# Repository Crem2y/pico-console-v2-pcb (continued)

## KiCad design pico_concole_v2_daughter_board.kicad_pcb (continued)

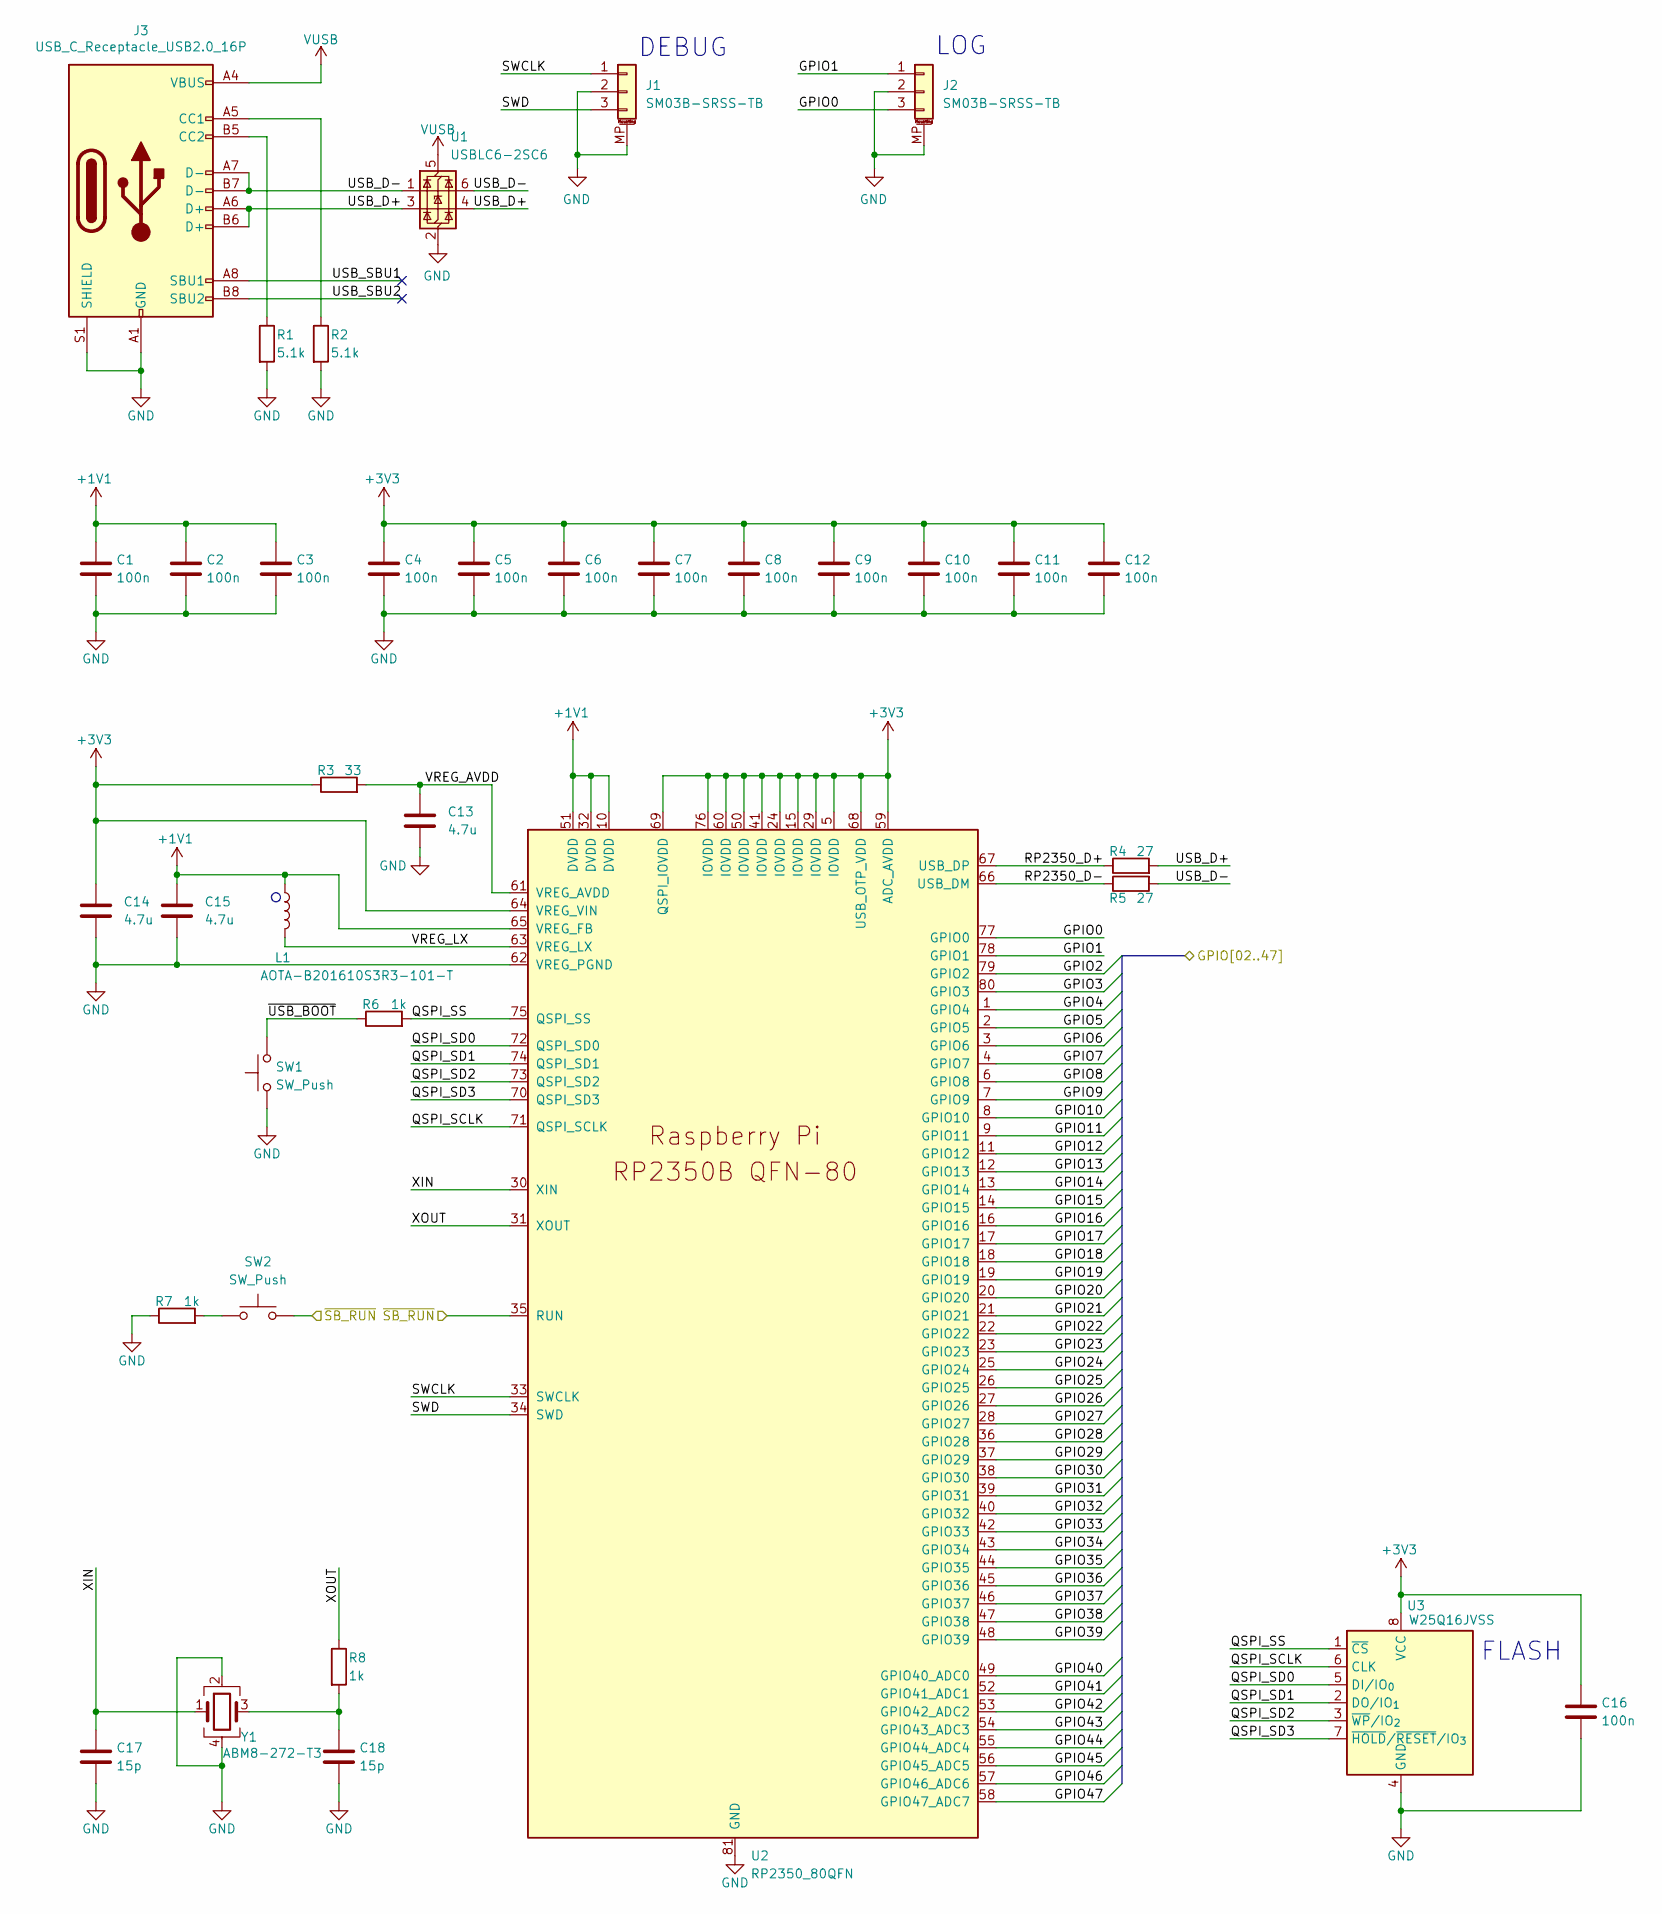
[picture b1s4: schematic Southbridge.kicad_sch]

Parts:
C1, C2, C3, C4, C5, C6, C7, C8, C9, C10, C11, C12, C16: 100n; C_0402_1005Metric_Pad0.74x0.62mm_HandSolder
C13, C14, C15: 4.7u; C_0603_1608Metric_Pad1.08x0.95mm_HandSolder
C17, C18: 15p; C_0402_1005Metric_Pad0.74x0.62mm_HandSolder
J1, J2: SM03B-SRSS-TB; JST_SH_SM03B-SRSS-TB_1x03-1MP_P1.00mm_Horizontal
J3: USB_C_Receptacle_USB2.0_16P; USB_C_Receptacle_HRO_TYPE-C-31-M-12
L1: AOTA-B201610S3R3-101-T; L_pol_2016
R1, R2: 5.1k; R_0805_2012Metric_Pad1.20x1.40mm_HandSolder
R3: 33; C_0402_1005Metric_Pad0.74x0.62mm_HandSolder
R4, R5: 27; R_0402_1005Metric_Pad0.72x0.64mm_HandSolder
R6, R7, R8: 1k; R_0402_1005Metric_Pad0.72x0.64mm_HandSolder
SW1, SW2: SW_Push; SW_Push_1P1T_NO_Vertical_Wuerth_434133025816
U1: USBLC6-2SC6; SOT-23-6
U2: RP2350_80QFN; QFN-80-1EP_10x10mm_P0.4mm_EP3.4x3.4mm; LCSC PN C42415655
U3: W25Q16JVSS; SOIC-8_5.3x5.3mm_P1.27mm
Y1: ABM8-272-T3; Crystal_SMD_3225-4Pin_3.2x2.5mm; LCSC PN C20625731

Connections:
+1V1: C1.1, C2.1, C3.1, C15.1, L1.1, U2.10 (DVDD), U2.32 (DVDD), U2.51 (DVDD), U2.65 (VREG_FB)
+3V3: C4.1, C5.1, C6.1, C7.1, C8.1, C9.1, C10.1, C11.1, C12.1, C14.1, C16.1, R3.1, U2.5 (IOVDD), U2.15 (IOVDD), U2.24 (IOVDD), U2.29 (IOVDD), U2.41 (IOVDD), U2.50 (IOVDD), U2.59 (ADC_AVDD), U2.60 (IOVDD), U2.64 (VREG_VIN), U2.68 (USB_OTP_VDD), U2.69 (QSPI_IOVDD), U2.76 (IOVDD), U3.8 (VCC); also elsewhere on the board
/Daughterboard/GPIO2: U2.79 (GPIO2); also elsewhere on the board
/Daughterboard/GPIO3: U2.80 (GPIO3); also elsewhere on the board
/Daughterboard/GPIO6: U2.3 (GPIO6); also elsewhere on the board
/Daughterboard/GPIO7: U2.4 (GPIO7); also elsewhere on the board
/Daughterboard/GPIO8: U2.6 (GPIO8); also elsewhere on the board
/Daughterboard/GPIO9: U2.7 (GPIO9); also elsewhere on the board
/Daughterboard/GPIO10: U2.8 (GPIO10); also elsewhere on the board
/Daughterboard/GPIO11: U2.9 (GPIO11); also elsewhere on the board
/Daughterboard/GPIO12: U2.11 (GPIO12); also elsewhere on the board
/Daughterboard/GPIO13: U2.12 (GPIO13); also elsewhere on the board
/Daughterboard/GPIO14: U2.13 (GPIO14); also elsewhere on the board
/Daughterboard/GPIO15: U2.14 (GPIO15); also elsewhere on the board
/Daughterboard/GPIO16: U2.16 (GPIO16); also elsewhere on the board
/Daughterboard/GPIO17: U2.17 (GPIO17); also elsewhere on the board
/Daughterboard/GPIO18: U2.18 (GPIO18); also elsewhere on the board
/Daughterboard/GPIO19: U2.19 (GPIO19); also elsewhere on the board
/Daughterboard/GPIO20: U2.20 (GPIO20); also elsewhere on the board
/Daughterboard/GPIO21: U2.21 (GPIO21); also elsewhere on the board
/Daughterboard/GPIO22: U2.22 (GPIO22); also elsewhere on the board
/Daughterboard/GPIO23: U2.23 (GPIO23); also elsewhere on the board
/Daughterboard/GPIO24: U2.25 (GPIO24); also elsewhere on the board
/Daughterboard/GPIO25: U2.26 (GPIO25); also elsewhere on the board
/Daughterboard/GPIO26: U2.27 (GPIO26); also elsewhere on the board
/Daughterboard/GPIO27: U2.28 (GPIO27); also elsewhere on the board
/Daughterboard/GPIO28: U2.36 (GPIO28); also elsewhere on the board
/Daughterboard/GPIO29: U2.37 (GPIO29); also elsewhere on the board
/Daughterboard/GPIO30: U2.38 (GPIO30); also elsewhere on the board
/Daughterboard/GPIO31: U2.39 (GPIO31); also elsewhere on the board
/Daughterboard/GPIO32: U2.40 (GPIO32); also elsewhere on the board
/Daughterboard/GPIO33: U2.42 (GPIO33); also elsewhere on the board
/Daughterboard/GPIO34: U2.43 (GPIO34); also elsewhere on the board
/Daughterboard/GPIO35: U2.44 (GPIO35); also elsewhere on the board
/Daughterboard/GPIO36: U2.45 (GPIO36); also elsewhere on the board
/Daughterboard/GPIO37: U2.46 (GPIO37); also elsewhere on the board
/Daughterboard/GPIO38: U2.47 (GPIO38); also elsewhere on the board
/Daughterboard/GPIO39: U2.48 (GPIO39); also elsewhere on the board
/Daughterboard/GPIO40: U2.49 (GPIO40_ADC0); also elsewhere on the board
/Daughterboard/GPIO41: U2.52 (GPIO41_ADC1); also elsewhere on the board
/Daughterboard/GPIO42: U2.53 (GPIO42_ADC2); also elsewhere on the board
/Daughterboard/GPIO43: U2.54 (GPIO43_ADC3); also elsewhere on the board
/Daughterboard/GPIO44: U2.55 (GPIO44_ADC4); also elsewhere on the board
/Daughterboard/GPIO45: U2.56 (GPIO45_ADC5); also elsewhere on the board
/Daughterboard/GPIO46: U2.57 (GPIO46_ADC6); also elsewhere on the board
/Daughterboard/GPIO47: U2.58 (GPIO47_ADC7); also elsewhere on the board
/Daughterboard/MAIN_GPIO12: U2.2 (GPIO5); also elsewhere on the board
/Daughterboard/MAIN_GPIO13: U2.1 (GPIO4); also elsewhere on the board
/Daughterboard/~SB_RUN: SW2.2, U2.35 (RUN); also elsewhere on the board
/Southbridge/GPIO0: J2.3, U2.77 (GPIO0)
/Southbridge/GPIO1: J2.1, U2.78 (GPIO1)
/Southbridge/QSPI_SCLK: U2.71 (QSPI_SCLK), U3.6 (CLK)
/Southbridge/QSPI_SD0: U2.72 (QSPI_SD0), U3.5 (DI/IO_{0})
/Southbridge/QSPI_SD1: U2.74 (QSPI_SD1), U3.2 (DO/IO_{1})
/Southbridge/QSPI_SD2: U2.73 (QSPI_SD2), U3.3 (~WP/IO_{2})
/Southbridge/QSPI_SD3: U2.70 (QSPI_SD3), U3.7 (~HOLD/~RESET/IO_{3})
/Southbridge/QSPI_SS: R6.2, U2.75 (QSPI_SS), U3.1 (~CS)
/Southbridge/RP2350_D+: R4.1, U2.67 (USB_DP)
/Southbridge/RP2350_D-: R5.1, U2.66 (USB_DM)
/Southbridge/SWCLK: J1.1, U2.33 (SWCLK)
/Southbridge/SWD: J1.3, U2.34 (SWD)
/Southbridge/USB_D+: J3.A6 (D+), J3.B6 (D+), R4.2, U1.3 (I/O2), U1.4 (I/O2)
/Southbridge/USB_D-: J3.A7 (D-), J3.B7 (D-), R5.2, U1.1 (I/O1), U1.6 (I/O1)
/Southbridge/USB_SBU1: J3.A8 (SBU1)
/Southbridge/USB_SBU2: J3.B8 (SBU2)
/Southbridge/VREG_AVDD: C13.1, R3.2, U2.61 (VREG_AVDD)
/Southbridge/VREG_LX: L1.2, U2.63 (VREG_LX)
/Southbridge/XIN: C17.1, U2.30 (XIN), Y1.1
/Southbridge/XOUT: R8.1, U2.31 (XOUT)
/Southbridge/~USB_BOOT: R6.1, SW1.2
GND: C1.2, C2.2, C3.2, C4.2, C5.2, C6.2, C7.2, C8.2, C9.2, C10.2, C11.2, C12.2, C13.2, C14.2, C15.2, C16.2, C17.2, C18.2, J1.2, J1.MP (MountPin), J2.2, J2.MP (MountPin), J3.A1 (GND), J3.A12 (GND), J3.B1 (GND), J3.B12 (GND), J3.S1 (SHIELD), R1.2, R2.2, R7.1, SW1.1, U1.2 (GND), U2.62 (VREG_PGND), U2.81 (GND), U3.4 (GND), Y1.2, Y1.4; also elsewhere on the board
unnamed: C18.1, R8.2, Y1.3
unnamed: J3.A5 (CC1), R2.1
unnamed: J3.B5 (CC2), R1.1
unnamed: R7.2, SW2.1
VUSB: J3.A4 (VBUS), J3.A9 (VBUS), J3.B4 (VBUS), J3.B9 (VBUS), U1.5 (VBUS); also elsewhere on the board

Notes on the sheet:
LOG
DEBUG
FLASH

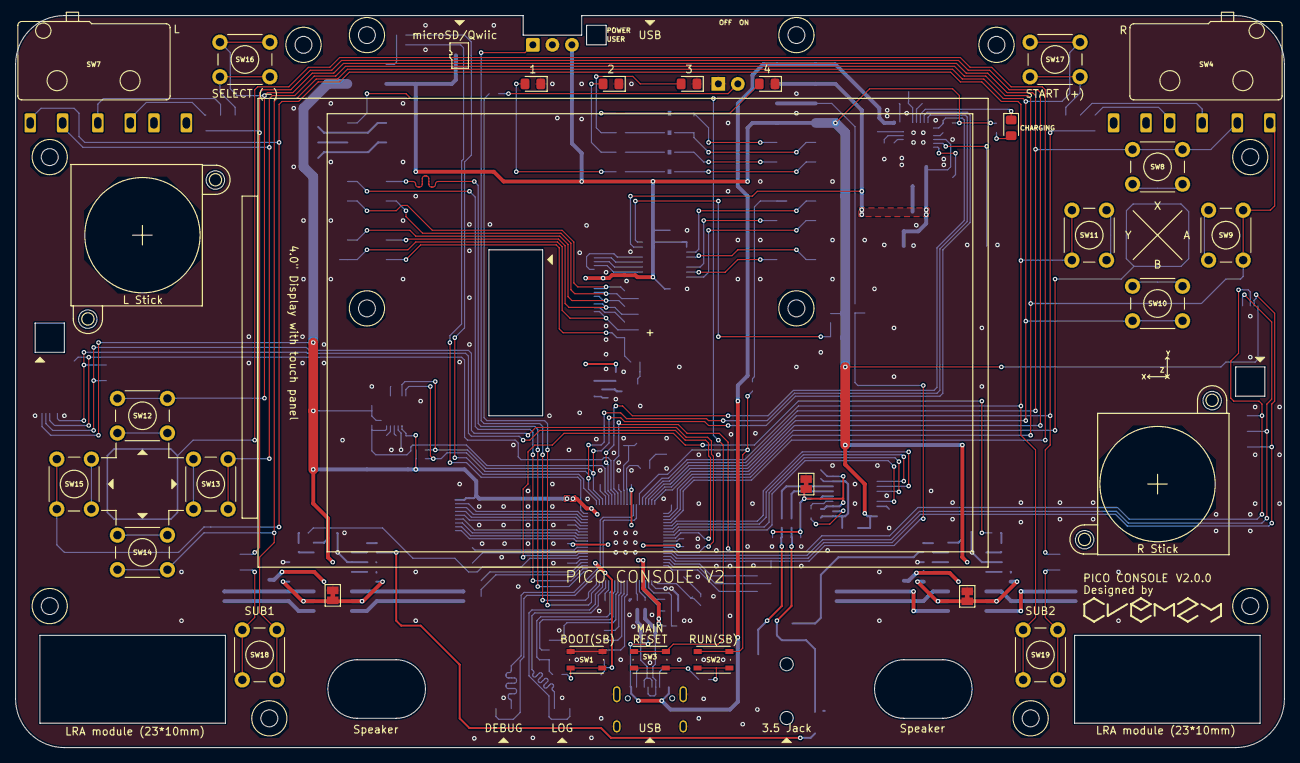
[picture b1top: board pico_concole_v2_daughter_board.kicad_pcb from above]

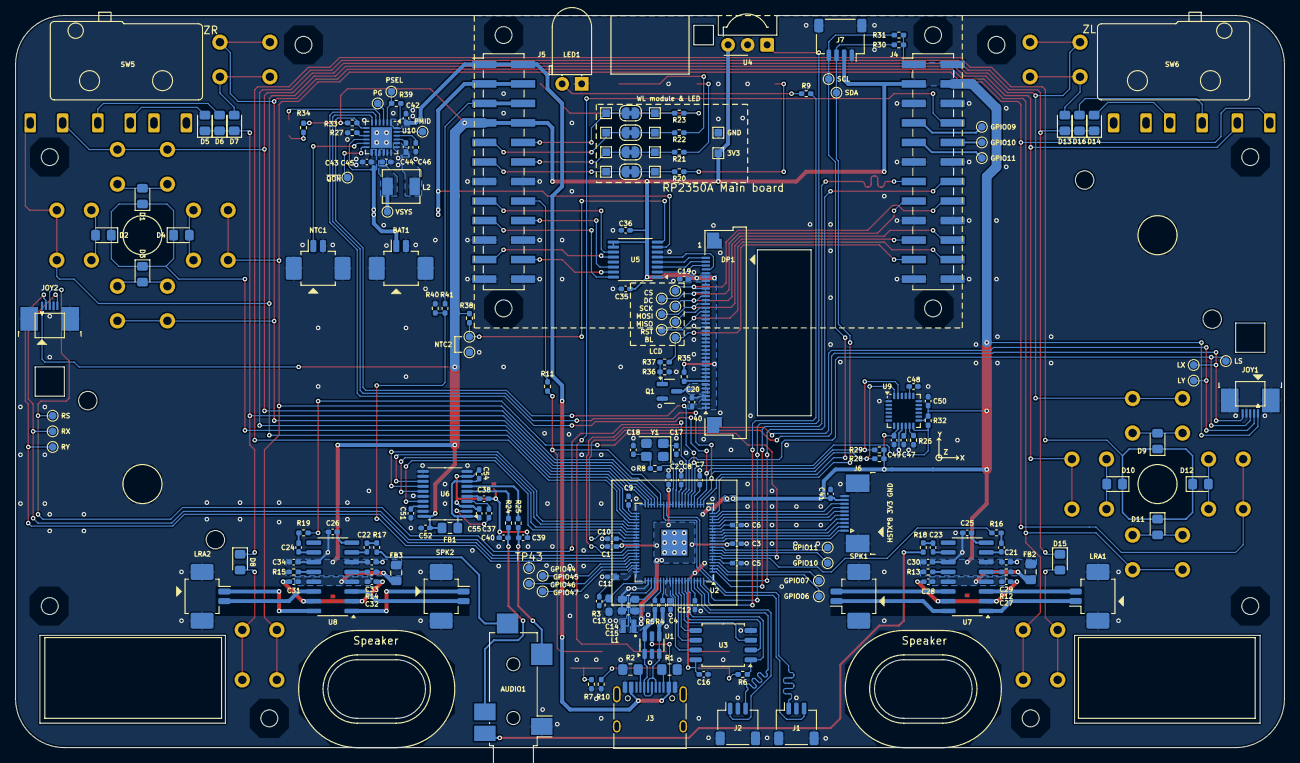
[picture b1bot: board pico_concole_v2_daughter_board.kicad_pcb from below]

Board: 2 copper layers, 165.1 x 95.2 mm, 232 parts (195 on the bottom side), 180 nets.

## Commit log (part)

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2026-04-11 V2.0.0 WIP
2026-04-12 Add switch footprint
2026-04-12 Place components temporarily
2026-04-21 Add footprint
2026-04-24 Remove unused footprint
2026-04-25 Update LCD pin assignments
2026-05-02 Add BQ25619 symbol
2026-05-03 routing complete
2026-05-03 Update BOM
2026-05-04 Update schematic - Change L2 - Add NTC2 pad - Connect pins to measure voltages
2026-05-12 Add documentation
